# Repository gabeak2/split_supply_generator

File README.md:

# split_supply_generator
A SMPS board to generate a +/-15V rail from 5V USB or 9-12V Barrel jack.  Uses switching regulators followed by linear ones, so noise performance is pretty good at ~1mVpp!

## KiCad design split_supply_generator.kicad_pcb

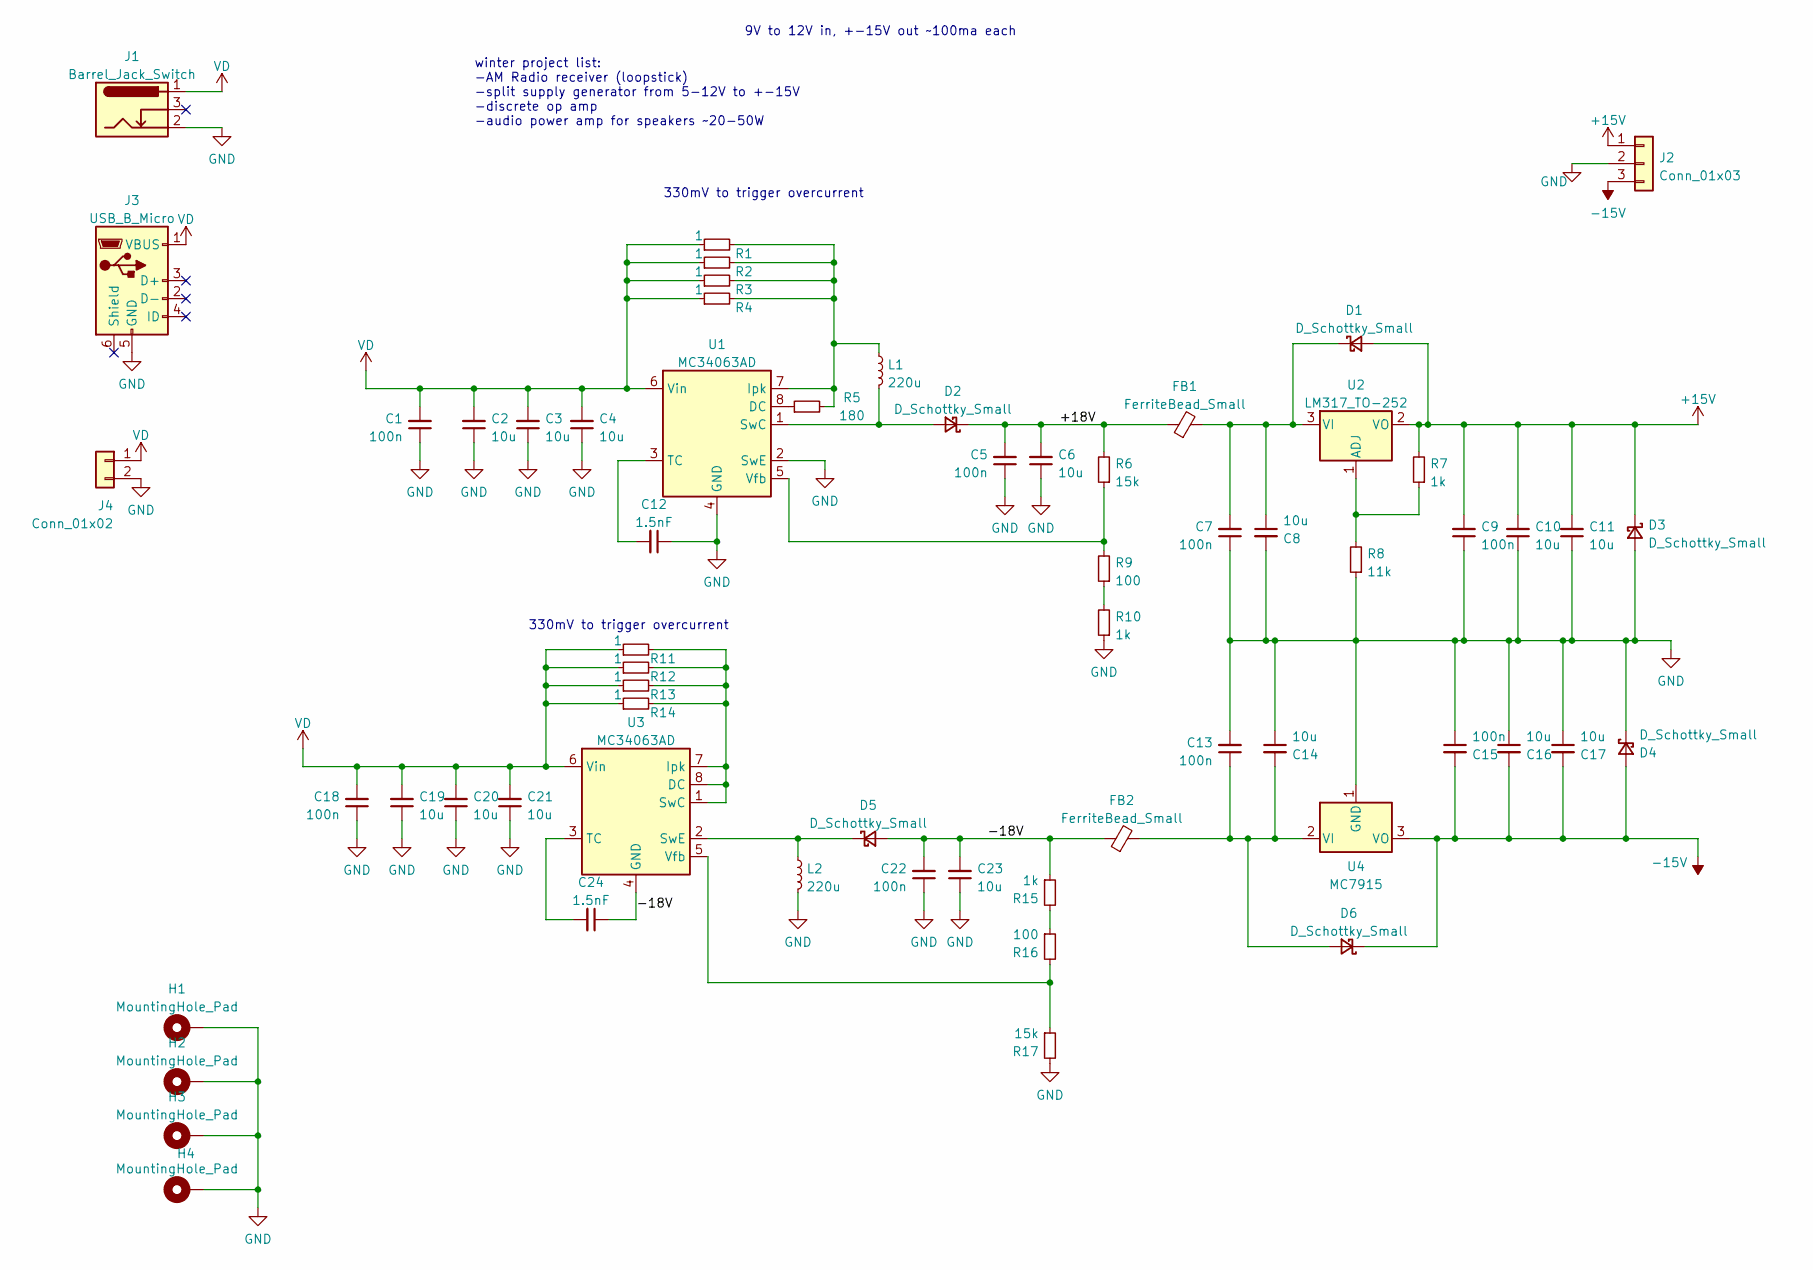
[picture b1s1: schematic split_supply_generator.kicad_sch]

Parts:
C1, C5, C7, C9, C13, C15, C18, C22: 100n; C_0805_2012Metric; LCSC PN C49678
C2, C3, C4, C6, C8, C10, C11, C14, C16, C17, C19, C20, C21, C23: 10u; C_0805_2012Metric; LCSC PN C440198
C12, C24: 1.5nF; C_0805_2012Metric; LCSC PN C1717
D1, D2, D3, D4, D5, D6: D_Schottky_Small; D_SOD-123; LCSC PN C8598
FB1, FB2: FerriteBead_Small; L_0805_2012Metric; LCSC PN C1017
H1, H2, H3, H4: MountingHole_Pad; MountingHole_2.2mm_M2_DIN965_Pad
J1: Barrel_Jack_Switch; BarrelJack_GCT_DCJ200-10-A_Horizontal
J2: Conn_01x03; PinSocket_1x03_P2.54mm_Vertical
J3: USB_B_Micro; USB_Micro-B_Molex-105017-0001
J4: Conn_01x02; PinSocket_1x02_P2.54mm_Vertical
L1, L2: 220u; ind_SWRB1207S-221MT; LCSC PN C169380
R1, R2, R3, R4, R11, R12, R13, R14: 1; R_0805_2012Metric; LCSC PN C25271
R5: 180; R_0805_2012Metric; LCSC PN C25270
R6, R17: 15k; R_0805_2012Metric; LCSC PN C17475
R7, R10, R15: 1k; R_0805_2012Metric; LCSC PN C17513
R8: 11k; R_0805_2012Metric; LCSC PN C17429
R9, R16: 100; R_0805_2012Metric; LCSC PN C17408
U1, U3: MC34063AD; SOIC-8_3.9x4.9mm_P1.27mm; LCSC PN C32078
U2: LM317_TO-252; TO-252-2
U4: MC7915; TO-263-2

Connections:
+15V: C9.2, C10.2, C11.2, D1.2 (A), D3.1 (K), J2.1, R7.2, U2.2 (VO)
-15V: C15.2, C16.2, C17.2, D4.2 (A), D6.1 (K), J2.3, U4.3 (VO)
/+18V: C5.2, C6.2, D2.1 (K), FB1.1, R6.2
/-18V: C22.2, C23.2, C24.1, D5.2 (A), FB2.1, R15.1, U3.4 (GND)
GND: C1.1, C2.1, C3.1, C4.1, C5.1, C6.1, C7.1, C8.2, C9.1, C10.1, C11.1, C12.1, C13.2, C14.1, C15.1, C16.1, C17.1, C18.1, C19.1, C20.1, C21.1, C22.1, C23.1, D3.2 (A), D4.1 (K), H1.1, H2.1, H3.1, H4.1, J1.2, J2.2, J3.5 (GND), J4.2, L2.2, R8.1, R10.1, R17.2, U1.2 (SwE), U1.4 (GND), U4.1 (GND)
unnamed: C7.2, C8.1, D1.1 (K), FB1.2, U2.3 (VI)
unnamed: C12.2, U1.3 (TC)
unnamed: C13.1, C14.2, D6.2 (A), FB2.2, U4.2 (VI)
unnamed: C24.2, U3.3 (TC)
unnamed: D2.2 (A), L1.2, U1.1 (SwC)
unnamed: D5.1 (K), L2.1, U3.2 (SwE)
unnamed: L1.1, R1.2, R2.2, R3.2, R4.2, R5.2, U1.7 (Ipk)
unnamed: R5.1, U1.8 (DC)
unnamed: R6.1, R9.2, U1.5 (Vfb)
unnamed: R7.1, R8.2, U2.1 (ADJ)
unnamed: R9.1, R10.2
unnamed: R11.2, R12.2, R13.2, R14.2, U3.1 (SwC), U3.7 (Ipk), U3.8 (DC)
unnamed: R15.2, R16.1
unnamed: R16.2, R17.1, U3.5 (Vfb)
VD: C1.2, C2.2, C3.2, C4.2, C18.2, C19.2, C20.2, C21.2, J1.1, J3.1 (VBUS), J4.1, R1.1, R2.1, R3.1, R4.1, R11.1, R12.1, R13.1, R14.1, U1.6 (Vin), U3.6 (Vin)

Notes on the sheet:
9V to 12V in, +-15V out ~100ma each
winter project list: -AM Radio receiver (loopstick) -split supply generator from 5-12V to +-15V -discrete op amp -audio power amp for speakers ~20-50W
330mV to trigger overcurrent

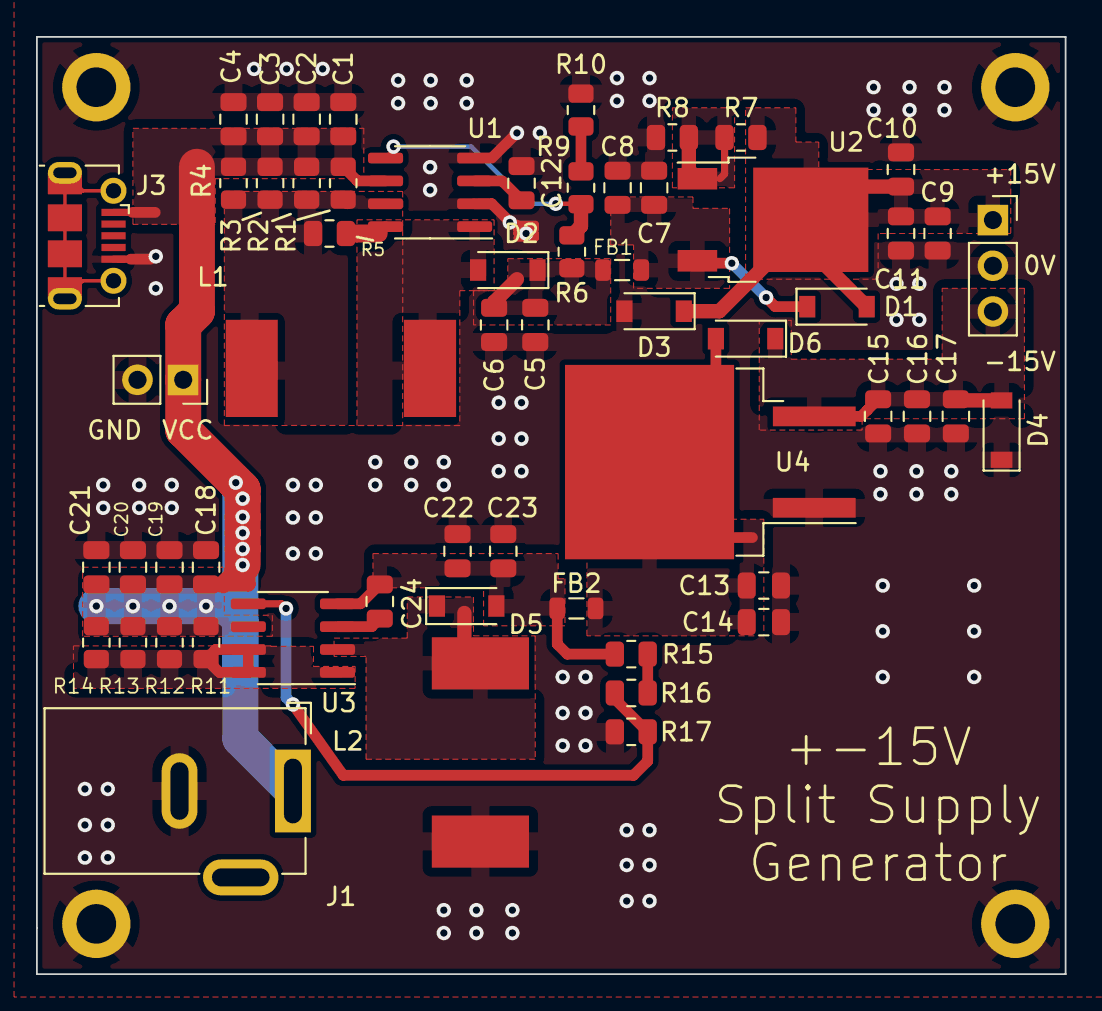
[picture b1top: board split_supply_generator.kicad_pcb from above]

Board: 2 copper layers, 57.1 x 52.1 mm, 63 parts (0 on the bottom side), 20 nets.

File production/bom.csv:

Designator,Footprint,Quantity,Value,LCSC Part #
"C1, C13, C15, C18, C22, C5, C7, C9",C_0805_2012Metric,8,100n,
"C10, C11, C14, C16, C17, C19, C2, C20, C21, C23, C3, C4, C6, C8",C_0805_2012Metric,14,10u,
"C12, C24",C_0805_2012Metric,2,1.5nF,
"D1, D2, D3, D4, D5, D6",D_SOD-123,6,D_Schottky_Small,
"FB1, FB2",L_0805_2012Metric,2,FerriteBead_Small,
"H1, H2, H3, H4",MountingHole_2.2mm_M2_DIN965_Pad,4,MountingHole_Pad,
J1,BarrelJack_GCT_DCJ200-10-A_Horizontal,1,Barrel_Jack_Switch,
J2,PinSocket_1x03_P2.54mm_Vertical,1,Conn_01x03,
J3,USB_Micro-B_Molex-105017-0001,1,USB_B_Micro,
J4,PinSocket_1x02_P2.54mm_Vertical,1,Conn_01x02,
"L1, L2",ind_SWRB1207S-221MT,2,220u,
"R1, R11, R12, R13, R14, R2, R3, R4",R_0805_2012Metric,8,1,
"R10, R15, R7",R_0805_2012Metric,3,1k,
"R16, R9",R_0805_2012Metric,2,100,
"R17, R6",R_0805_2012Metric,2,15k,
R5,R_0805_2012Metric,1,180,
R8,R_0805_2012Metric,1,11k,
"U1, U3",SOIC-8_3.9x4.9mm_P1.27mm,2,MC34063AD,
U2,TO-252-2,1,LM317_TO-252,
U4,TO-263-2,1,MC7915,
